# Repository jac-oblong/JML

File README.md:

# jml-16
16-bit computer built from scrap

## Design
The computer is designed in individual sections that come together to create the
whole system. This is useful as it makes changing a section easy.

## Parts
All parts have been scrapped from other computers/electronics. Using different
parts will likely produce a better computer.

### Changing parts
The high-level for this computer is designed in such a way that parts can easily
be swapped out for a different component with similar functionality. For 
example, the vga display driver can be swapped out for a different driver as
long as the inputs and outputs stay consistent.

Obviously, the hardware within specific modules cannot be swapped out as easily
without fully ensuring similar functionality.

## Folder Organization
Datasheets for parts, in addition to general documentation about the entire
project can be found in the [docs](/docs/) directory.

The assembler used to convert assembly to machine code can be found in the
[assembler](/assembler/) directory.

<!--
The compiler used to compile C code can be found in the [compiler](/compiler/)
directory.
-->

Information about the keyboard interface can be found in [keyboard](/keyboard/).

Information about the monitor interface can be found in [monitor](/monitor/).

Information about the different central computers can be found in any dirctory 
titled **jml-XX**.

Links to programs designed to be run on the **jml** family of computers can be 
found in [programs](/programs/)

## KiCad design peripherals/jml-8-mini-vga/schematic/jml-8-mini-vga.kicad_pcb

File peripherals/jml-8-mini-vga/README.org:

* JML-8-Mini VGA

#+ATTR_HTML: :width 600px
[[./schematic/jml-8-mini-vga.png]]

This provides a VGA interface to the JML-8-Mini via a Tang Nano 9k FPGA.
The daughterboard plugs into the the Z80 header pins on the JML-8-Mini.

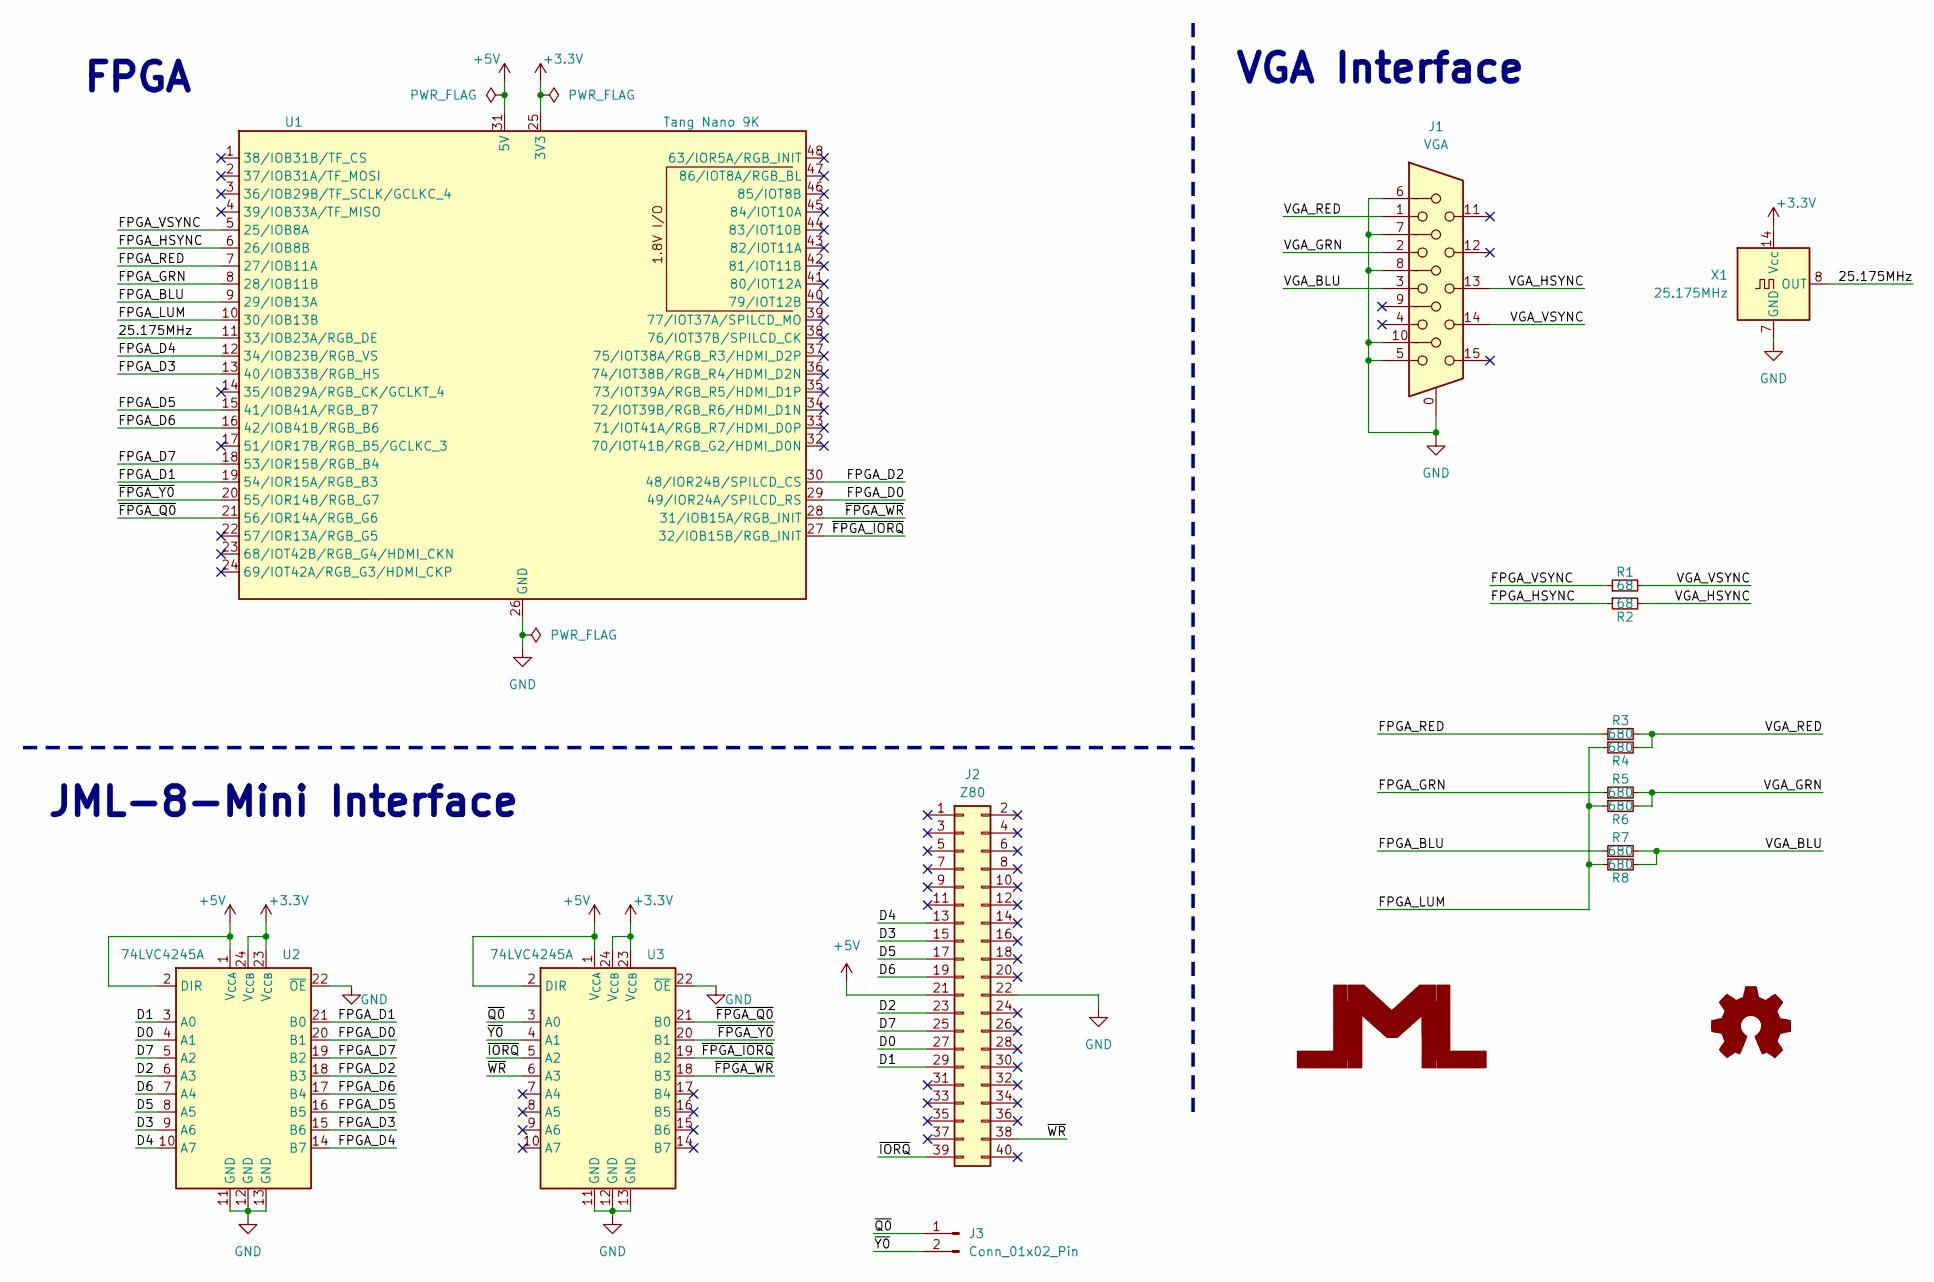
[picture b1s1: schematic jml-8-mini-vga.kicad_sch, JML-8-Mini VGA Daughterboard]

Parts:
J1: VGA; DSUB-15-HD_Female_Horizontal_P2.29x1.98mm_EdgePinOffset8.35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
J2: Z80; PinHeader_2x20_P2.54mm_Vertical
J3: Conn_01x02_Pin; PinHeader_1x02_P2.54mm_Vertical
R1, R2: 68; R_0805_2012Metric_Pad1.20x1.40mm_HandSolder
R3, R4, R5, R6, R7, R8: 680; R_0805_2012Metric_Pad1.20x1.40mm_HandSolder
U1: Tang Nano 9K; TangNano9k
U2, U3: 74LVC4245A; TSSOP-24_4.4x7.8mm_P0.65mm
X1: 25.175MHz; Oscillator_DIP-14

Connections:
+3.3V: U1.25 (3V3), U2.23 (V_{CCB}), U2.24 (V_{CCB}), U3.23 (V_{CCB}), U3.24 (V_{CCB}), X1.14 (Vcc)
+5V: J2.21, U1.31 (5V), U2.1 (V_{CCA}), U2.2 (DIR), U3.1 (V_{CCA}), U3.2 (DIR)
/25.175MHz: U1.11 (33/IOB23A/RGB_DE), X1.8 (OUT)
/D0: J2.27, U2.4 (A1)
/D1: J2.29, U2.3 (A0)
/D2: J2.23, U2.6 (A3)
/D3: J2.15, U2.9 (A6)
/D4: J2.13, U2.10 (A7)
/D5: J2.17, U2.8 (A5)
/D6: J2.19, U2.7 (A4)
/D7: J2.25, U2.5 (A2)
/FPGA_BLU: R7.1, U1.9 (29/IOB13A)
/FPGA_D0: U1.29 (49/IOR24A/SPILCD_RS), U2.20 (B1)
/FPGA_D1: U1.19 (54/IOR15A/RGB_B3), U2.21 (B0)
/FPGA_D2: U1.30 (48/IOR24B/SPILCD_CS), U2.18 (B3)
/FPGA_D3: U1.13 (40/IOB33B/RGB_HS), U2.15 (B6)
/FPGA_D4: U1.12 (34/IOB23B/RGB_VS), U2.14 (B7)
/FPGA_D5: U1.15 (41/IOB41A/RGB_B7), U2.16 (B5)
/FPGA_D6: U1.16 (42/IOB41B/RGB_B6), U2.17 (B4)
/FPGA_D7: U1.18 (53/IOR15B/RGB_B4), U2.19 (B2)
/FPGA_GRN: R5.1, U1.8 (28/IOB11B)
/FPGA_HSYNC: R2.1, U1.6 (26/IOB8B)
/FPGA_LUM: R4.1, R6.1, R8.1, U1.10 (30/IOB13B)
/FPGA_RED: R3.1, U1.7 (27/IOB11A)
/FPGA_VSYNC: R1.1, U1.5 (25/IOB8A)
/VGA_BLU: J1.3, R7.2, R8.2
/VGA_GRN: J1.2, R5.2, R6.2
/VGA_HSYNC: J1.13, R2.2
/VGA_RED: J1.1, R3.2, R4.2
/VGA_VSYNC: J1.14, R1.2
/~FPGA_IORQ: U1.27 (32/IOB15B/RGB_INIT), U3.19 (B2)
/~FPGA_Q0: U1.21 (56/IOR14A/RGB_G6), U3.21 (B0)
/~FPGA_WR: U1.28 (31/IOB15A/RGB_INIT), U3.18 (B3)
/~FPGA_Y0: U1.20 (55/IOR14B/RGB_G7), U3.20 (B1)
/~IORQ: J2.39, U3.5 (A2)
/~Q0: J3.1, U3.3 (A0)
/~WR: J2.38, U3.6 (A3)
/~Y0: J3.2, U3.4 (A1)
GND: J1.0, J1.5, J1.6, J1.7, J1.8, J1.10, J2.22, U1.26 (GND), U2.11 (GND), U2.12 (GND), U2.13 (GND), U2.22 (~OE), U3.11 (GND), U3.12 (GND), U3.13 (GND), U3.22 (~OE), X1.7 (GND)

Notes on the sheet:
VGA Interface
JML-8-Mini Interface
FPGA

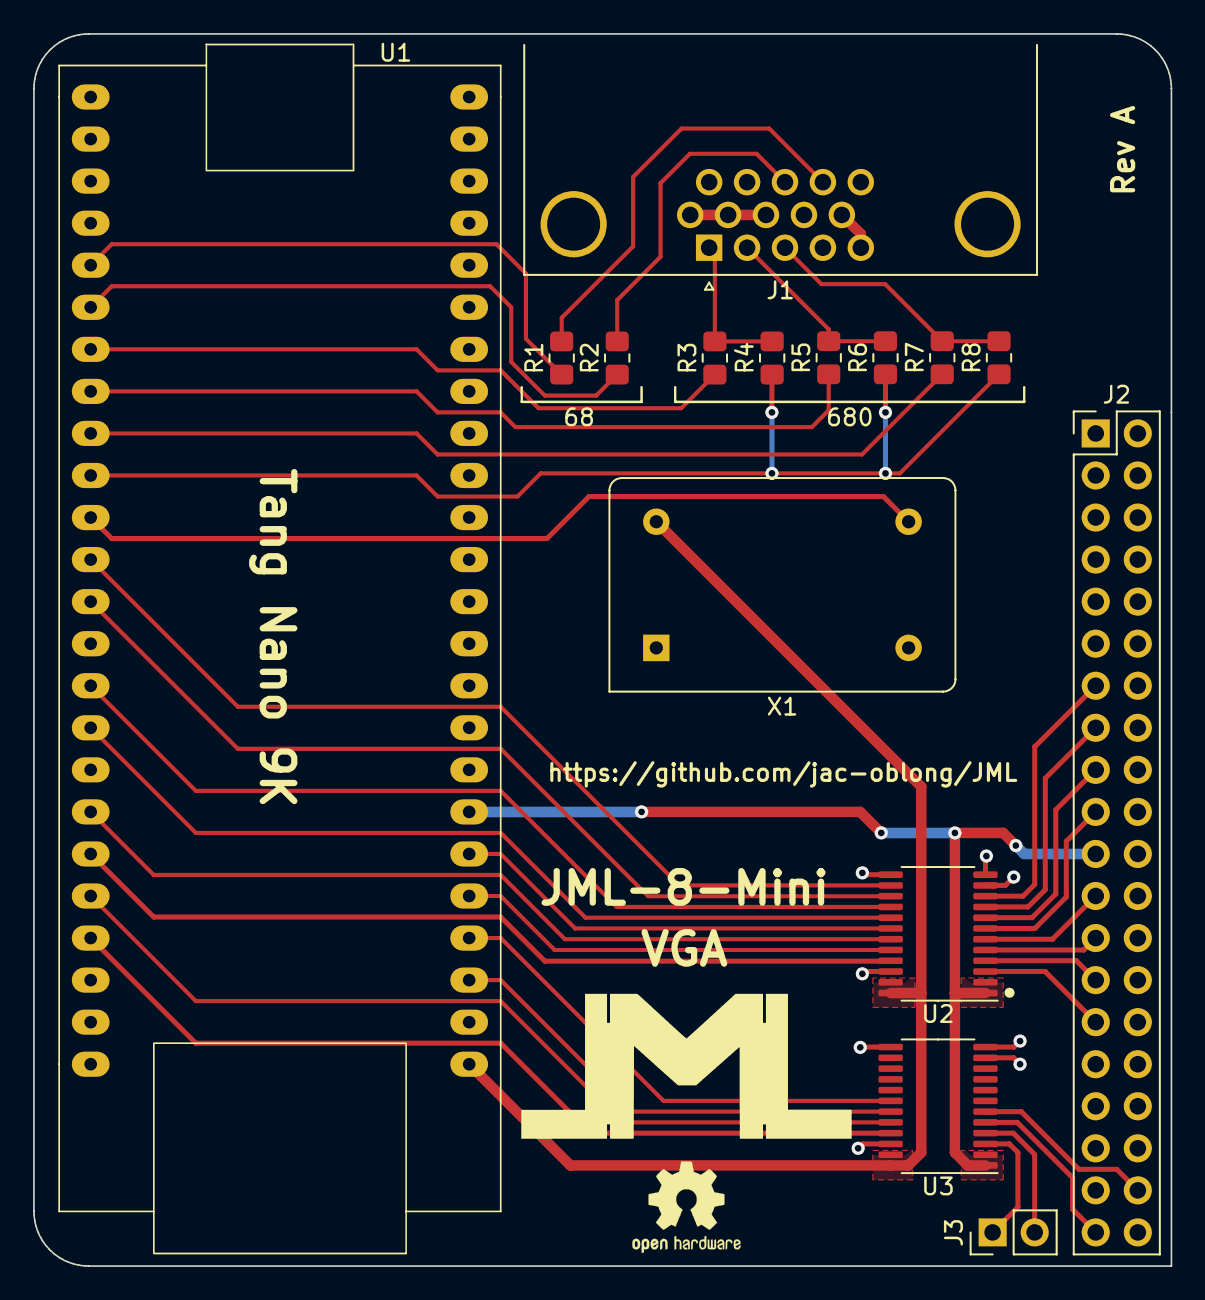
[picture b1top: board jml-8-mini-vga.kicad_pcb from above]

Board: 2 copper layers, 68.7 x 74.4 mm, 15 parts (0 on the bottom side), 39 nets.

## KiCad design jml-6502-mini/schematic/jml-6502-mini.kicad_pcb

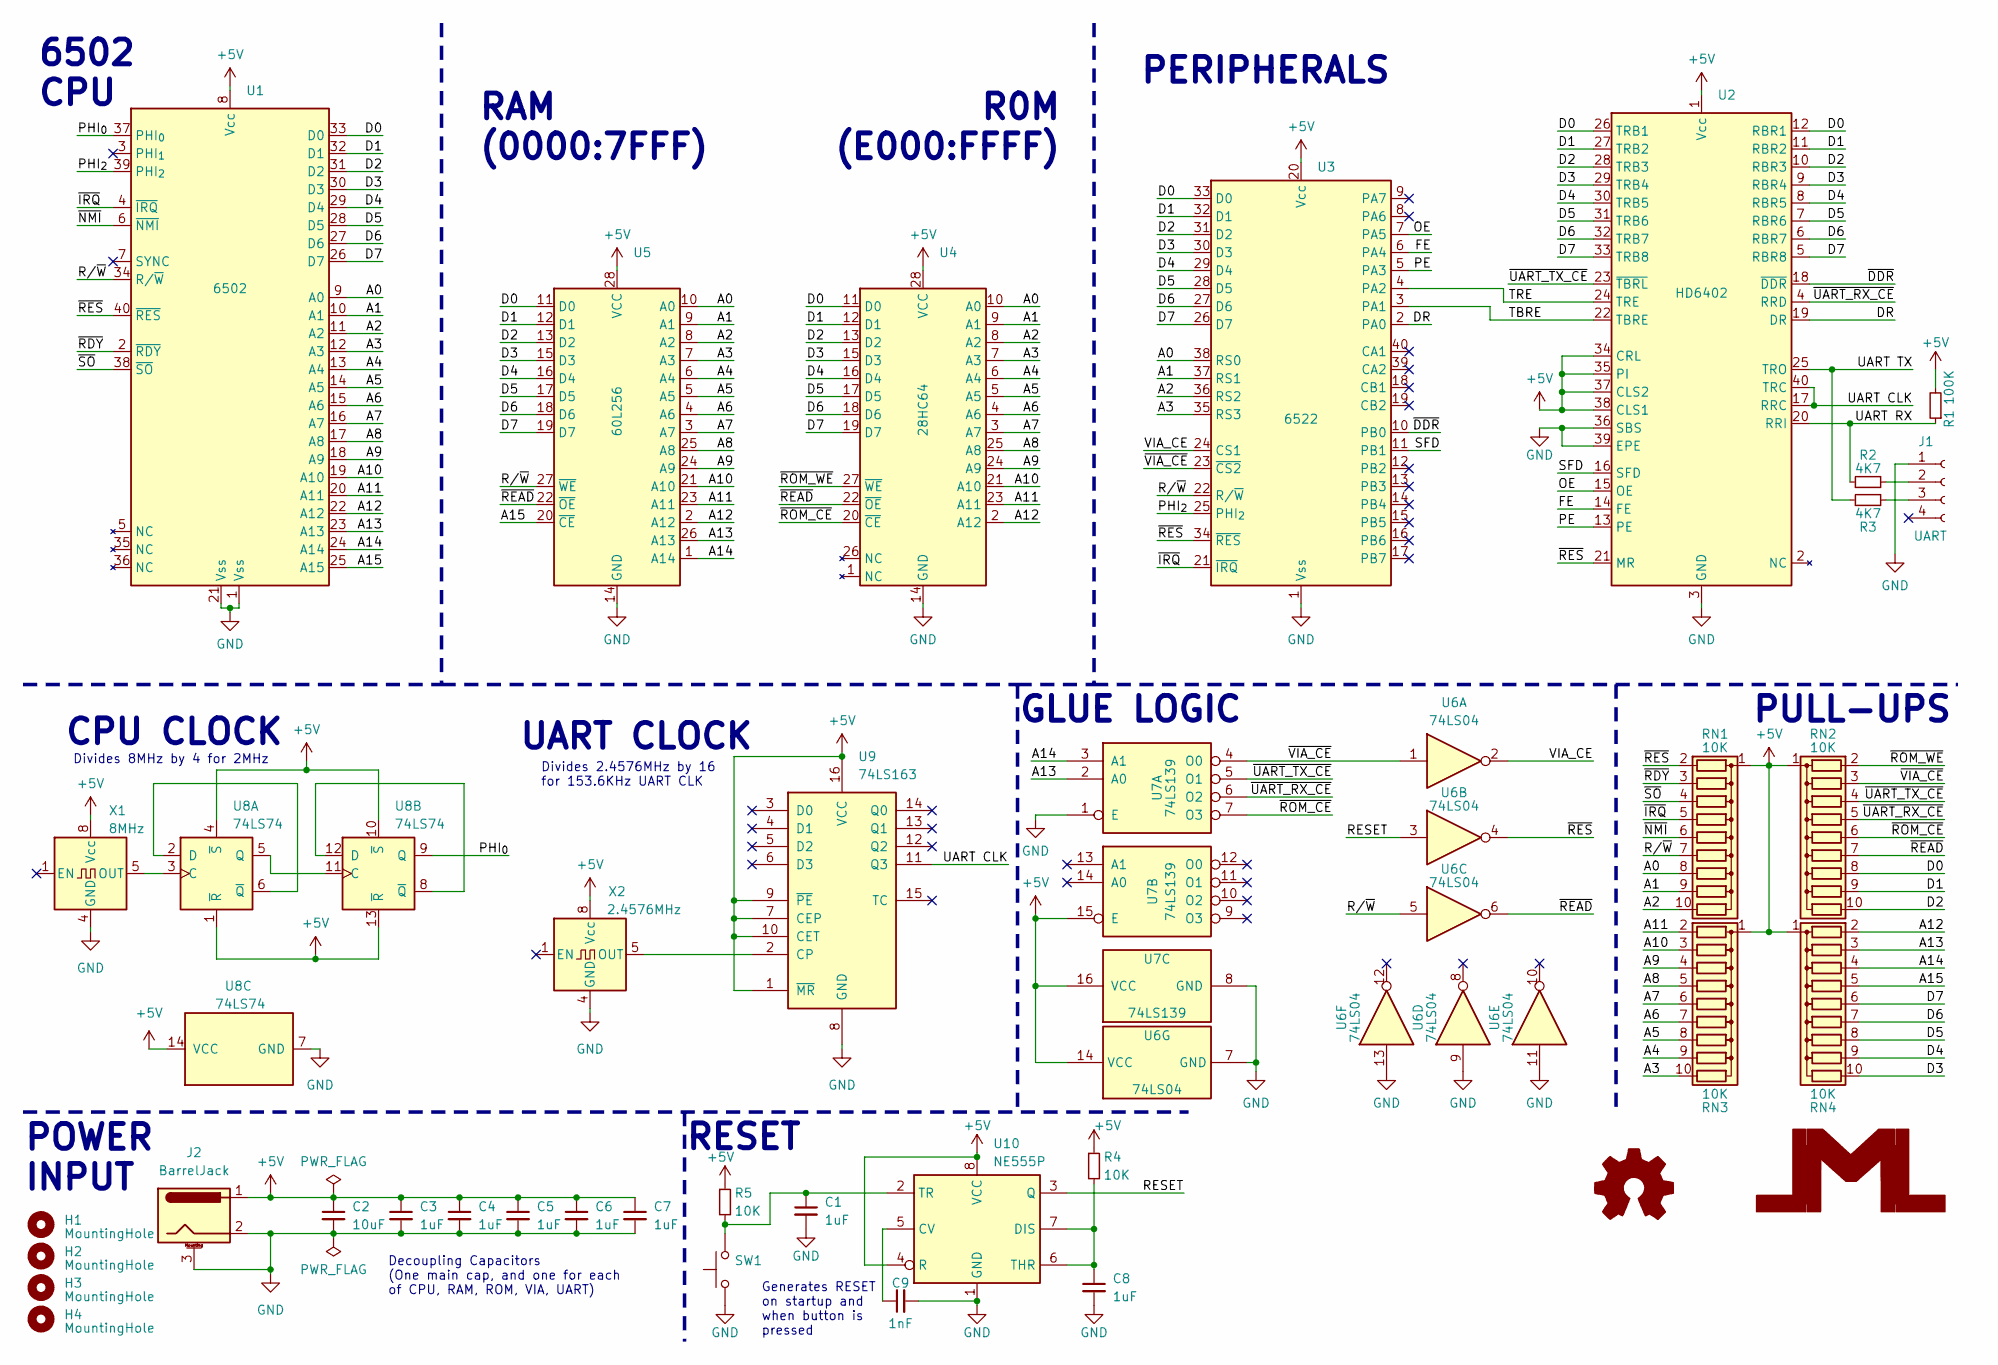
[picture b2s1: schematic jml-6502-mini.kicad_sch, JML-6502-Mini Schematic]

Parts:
C1, C3, C4, C5, C6, C7, C8: 1uF; C_Disc_D5.0mm_W2.5mm_P5.00mm
C2: 10uF; C_Radial_D5.0mm_H11.0mm_P2.00mm
C9: 1nF; C_Disc_D5.0mm_W2.5mm_P5.00mm
H1, H2, H3, H4: MountingHole; MountingHole_2.7mm_M2.5
J1: UART; PinHeader_1x04_P2.54mm_Horizontal
J2: BarrelJack; BarrelJack_Horizontal
R1: 100K; R_Axial_DIN0207_L6.3mm_D2.5mm_P7.62mm_Horizontal
R2, R3: 4K7; R_Axial_DIN0207_L6.3mm_D2.5mm_P7.62mm_Horizontal
R4, R5: 10K; R_Axial_DIN0207_L6.3mm_D2.5mm_P7.62mm_Horizontal
RN1, RN2, RN3, RN4: 10K; R_Array_SIP10
SW1: SW_Tactile_Straight_KSA0Axx1LFTR
U1: 6502; DIP-40_W15.24mm_Socket_LongPads
U2: HD6402; DIP-40_W15.24mm_Socket_LongPads
U3: 6522; DIP-40_W15.24mm_Socket_LongPads
U4: 28HC64; DIP-28_W15.24mm_Socket_LongPads
U5: 60L256; DIP-28_W15.24mm_Socket_LongPads
U6: 74LS04; DIP-14_W7.62mm_Socket_LongPads
U7: 74LS139; DIP-16_W7.62mm_Socket_LongPads
U8: 74LS74; DIP-14_W7.62mm_Socket_LongPads
U9: 74LS163; DIP-16_W7.62mm_Socket_LongPads
U10: NE555P; DIP-8_W7.62mm_Socket_LongPads
X1: 8MHz; Oscillator_DIP-8
X2: 2.4576MHz; Oscillator_DIP-8

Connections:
+5V: C2.1, C3.1, C4.1, C5.1, C6.1, C7.1, J2.1, R1.2, R4.1, R5.1, RN1.1 (common), RN2.1 (common), RN3.1 (common), RN4.1 (common), U1.8 (Vcc), U2.1 (Vcc), U2.34 (CRL), U2.35 (PI), U2.37 (CLS2), U2.38 (CLS1), U3.20 (Vcc), U4.28 (VCC), U5.28 (VCC), U6.14 (VCC), U7.15 (E), U7.16 (VCC), U8.1 (~R), U8.4 (~S), U8.10 (~S), U8.13 (~R), U8.14 (VCC), U9.1 (~MR), U9.7 (CEP), U9.9 (~PE), U9.10 (CET), U9.16 (VCC), U10.4 (R), U10.8 (VCC), X1.8 (Vcc), X2.8 (Vcc)
/A0: RN1.8 (R7), U1.9 (A0), U3.38 (RS0), U4.10 (A0), U5.10 (A0)
/A1: RN1.9 (R8), U1.10 (A1), U3.37 (RS1), U4.9 (A1), U5.9 (A1)
/A2: RN1.10 (R9), U1.11 (A2), U3.36 (RS2), U4.8 (A2), U5.8 (A2)
/A3: RN3.10 (R9), U1.12 (A3), U3.35 (RS3), U4.7 (A3), U5.7 (A3)
/A4: RN3.9 (R8), U1.13 (A4), U4.6 (A4), U5.6 (A4)
/A5: RN3.8 (R7), U1.14 (A5), U4.5 (A5), U5.5 (A5)
/A6: RN3.7 (R6), U1.15 (A6), U4.4 (A6), U5.4 (A6)
/A7: RN3.6 (R5), U1.16 (A7), U4.3 (A7), U5.3 (A7)
/A8: RN3.5 (R4), U1.17 (A8), U4.25 (A8), U5.25 (A8)
/A9: RN3.4 (R3), U1.18 (A9), U4.24 (A9), U5.24 (A9)
/A10: RN3.3 (R2), U1.19 (A10), U4.21 (A10), U5.21 (A10)
/A11: RN3.2 (R1), U1.20 (A11), U4.23 (A11), U5.23 (A11)
/A12: RN4.2 (R1), U1.22 (A12), U4.2 (A12), U5.2 (A12)
/A13: RN4.3 (R2), U1.23 (A13), U5.26 (A13), U7.2 (A0)
/A14: RN4.4 (R3), U1.24 (A14), U5.1 (A14), U7.3 (A1)
/A15: RN4.5 (R4), U1.25 (A15), U5.20 (~CE)
/D0: RN2.8 (R7), U1.33 (D0), U2.12 (RBR1), U2.26 (TRB1), U3.33 (D0), U4.11 (D0), U5.11 (D0)
/D1: RN2.9 (R8), U1.32 (D1), U2.11 (RBR2), U2.27 (TRB2), U3.32 (D1), U4.12 (D1), U5.12 (D1)
/D2: RN2.10 (R9), U1.31 (D2), U2.10 (RBR3), U2.28 (TRB3), U3.31 (D2), U4.13 (D2), U5.13 (D2)
/D3: RN4.10 (R9), U1.30 (D3), U2.9 (RBR4), U2.29 (TRB4), U3.30 (D3), U4.15 (D3), U5.15 (D3)
/D4: RN4.9 (R8), U1.29 (D4), U2.8 (RBR5), U2.30 (TRB5), U3.29 (D4), U4.16 (D4), U5.16 (D4)
/D5: RN4.8 (R7), U1.28 (D5), U2.7 (RBR6), U2.31 (TRB6), U3.28 (D5), U4.17 (D5), U5.17 (D5)
/D6: RN4.7 (R6), U1.27 (D6), U2.6 (RBR7), U2.32 (TRB7), U3.27 (D6), U4.18 (D6), U5.18 (D6)
/D7: RN4.6 (R5), U1.26 (D7), U2.5 (RBR8), U2.33 (TRB8), U3.26 (D7), U4.19 (D7), U5.19 (D7)
/DR: U2.19 (DR), U3.2 (PA0)
/FE: U2.14 (FE), U3.6 (PA4)
/OE: U2.15 (OE), U3.7 (PA5)
/PE: U2.13 (PE), U3.5 (PA3)
/PHI_{0}: U1.37 (PHI_{0}), U8.9 (Q)
/PHI_{2}: U1.39 (PHI_{2}), U3.25 (PHI_{2})
/RESET: U6.3, U10.3 (Q)
/R/~W: RN1.7 (R6), U1.34 (R/~W), U3.22 (R/~W), U5.27 (~WE), U6.5
/SFD: U2.16 (SFD), U3.11 (PB1)
/TBRE: U2.22 (TBRE), U3.3 (PA1)
/TRE: U2.24 (TRE), U3.4 (PA2)
/UART CLK: U2.17 (RRC), U2.40 (TRC), U9.11 (Q3)
/UART RX: R1.1, R2.1, U2.20 (RRI)
/UART TX: R3.1, U2.25 (TRO)
/VIA_CE: U3.24 (CS1), U6.2
/~DDR: U2.18 (~DDR), U3.10 (PB0)
/~IRQ: RN1.5 (R4), U1.4 (~IRQ), U3.21 (~IRQ)
/~NMI: RN1.6 (R5), U1.6 (~NMI)
/~RDY: RN1.3 (R2), U1.2 (~RDY)
/~READ: RN2.7 (R6), U4.22 (~OE), U5.22 (~OE), U6.6
/~RES: RN1.2 (R1), U1.40 (~RES), U2.21 (MR), U3.34 (~RES), U6.4
/~ROM_CE: RN2.6 (R5), U4.20 (~CE), U7.7 (O3)
/~ROM_WE: RN2.2 (R1), U4.27 (~WE)
/~SO: RN1.4 (R3), U1.38 (~SO)
/~UART_RX_CE: RN2.5 (R4), U2.4 (RRD), U7.6 (O2)
/~UART_TX_CE: RN2.4 (R3), U2.23 (~TBRL), U7.5 (O1)
/~VIA_CE: RN2.3 (R2), U3.23 (~CS2), U6.1, U7.4 (O0)
GND: C1.2, C2.2, C3.2, C4.2, C5.2, C6.2, C7.2, C8.2, C9.2, J1.1, J2.2, J2.3 (MountPin), SW1.1, U1.1 (Vss), U1.21 (Vss), U2.3 (GND), U2.36 (SBS), U2.39 (EPE), U3.1 (Vss), U4.14 (GND), U5.14 (GND), U6.7 (GND), U6.9, U6.11, U6.13, U7.1 (E), U7.8 (GND), U8.7 (GND), U9.8 (GND), U10.1 (GND), X1.4 (GND), X2.4 (GND)
unnamed: J1.2, R2.2
unnamed: J1.3, R3.2
unnamed: U8.3 (C), X1.5 (OUT)
unnamed: U8.2 (D), U8.6 (~Q)
unnamed: U8.5 (Q), U8.11 (C)
unnamed: U8.8 (~Q), U8.12 (D)
unnamed: U9.2 (CP), X2.5 (OUT)
unnamed: C9.1, U10.5 (CV)
unnamed: C8.1, R4.2, U10.6 (THR), U10.7 (DIS)
unnamed: C1.1, R5.2, SW1.2, U10.2 (TR)

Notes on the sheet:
GLUE LOGIC
RAM (0000:7FFF)
R0M (E000:FFFF)
RESET
Generates RESET on startup and when button is pressed
Divides 8MHz by 4 for 2MHz
CPU CLOCK
POWER INPUT
UART CLOCK
Decoupling Capacitors (One main cap, and one for each of CPU, RAM, ROM, VIA, UART)
Divides 2.4576MHz by 16 for 153.6KHz UART CLK
6502 CPU
PULL-UPS
PERIPHERALS

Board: 4 copper layers, 37 parts (0 on the bottom side), 63 nets, no tracks yet.

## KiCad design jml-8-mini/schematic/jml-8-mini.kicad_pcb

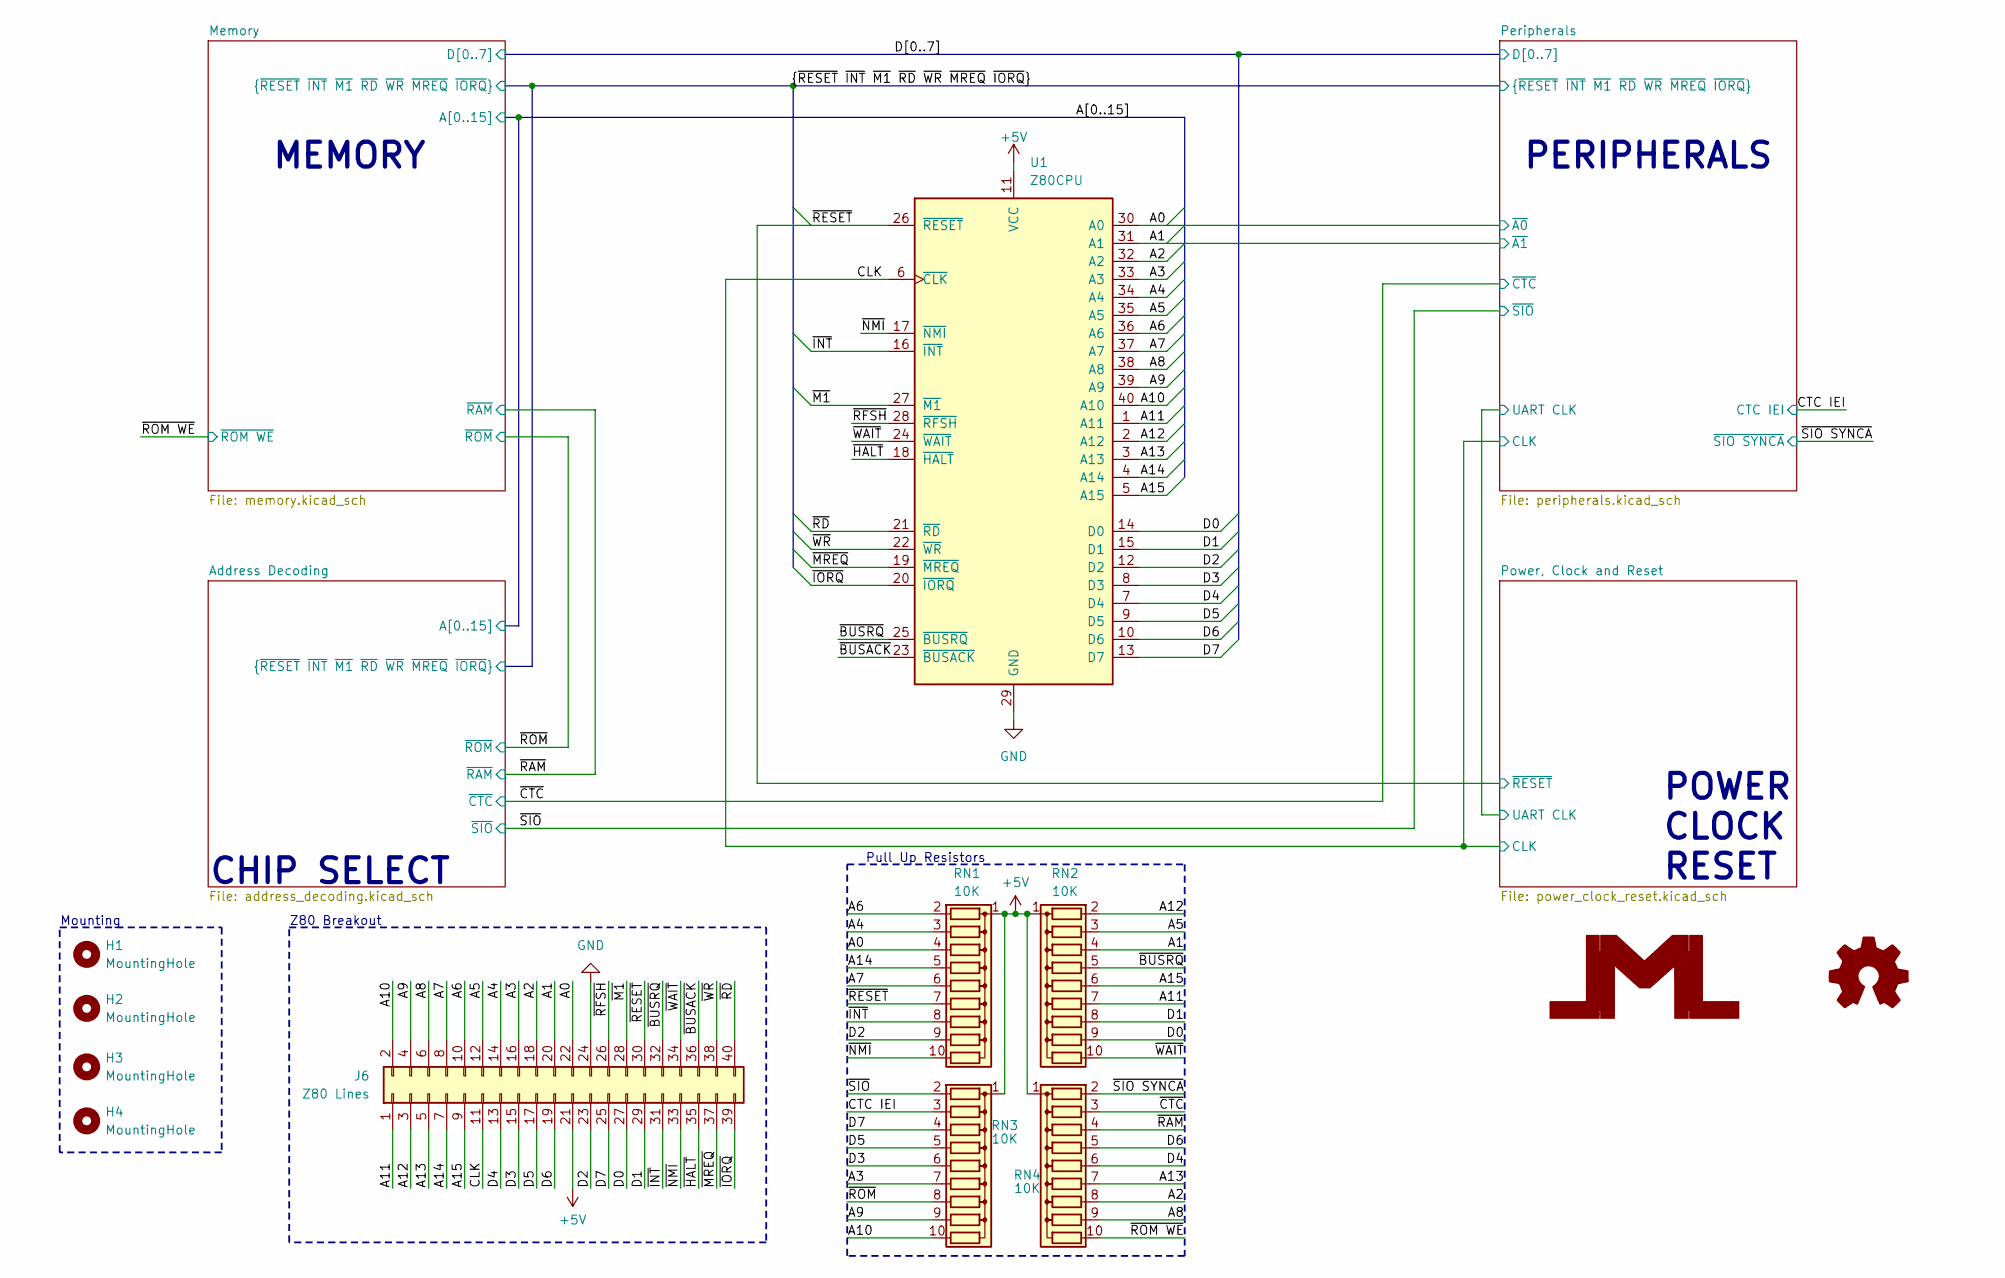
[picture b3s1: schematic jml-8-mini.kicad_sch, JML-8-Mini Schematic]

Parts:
H1, H2, H3, H4: MountingHole; MountingHole_2.7mm_M2.5
J6: Z80 Lines; PinHeader_2x20_P2.54mm_Vertical
RN1, RN2, RN3, RN4: 10K; R_Array_SIP10
U1: Z80CPU; DIP-40_W15.24mm_Socket_LongPads

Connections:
/A0: J6.22, RN1.4 (R3), U1.30 (A0); also elsewhere on the board
/A1: J6.20, RN2.4 (R3), U1.31 (A1); also elsewhere on the board
/A2: J6.18, RN4.8 (R7), U1.32 (A2); also elsewhere on the board
/A3: J6.16, RN3.7 (R6), U1.33 (A3); also elsewhere on the board
/A4: J6.14, RN1.3 (R2), U1.34 (A4); also elsewhere on the board
/A5: J6.12, RN2.3 (R2), U1.35 (A5); also elsewhere on the board
/A6: J6.10, RN1.2 (R1), U1.36 (A6); also elsewhere on the board
/A7: J6.8, RN1.6 (R5), U1.37 (A7); also elsewhere on the board
/A8: J6.6, RN4.9 (R8), U1.38 (A8); also elsewhere on the board
/A9: J6.4, RN3.9 (R8), U1.39 (A9); also elsewhere on the board
/A10: J6.2, RN3.10 (R9), U1.40 (A10); also elsewhere on the board
/A11: J6.1, RN2.7 (R6), U1.1 (A11); also elsewhere on the board
/A12: J6.3, RN2.2 (R1), U1.2 (A12); also elsewhere on the board
/A13: J6.5, RN4.7 (R6), U1.3 (A13); also elsewhere on the board
/A14: J6.7, RN1.5 (R4), U1.4 (A14); also elsewhere on the board
/CLK: J6.11, U1.6 (~CLK); also elsewhere on the board
/CTC IEI: RN3.3 (R2); also elsewhere on the board
/D0: J6.27, RN2.9 (R8), U1.14 (D0); also elsewhere on the board
/D1: J6.29, RN2.8 (R7), U1.15 (D1); also elsewhere on the board
/D2: J6.23, RN1.9 (R8), U1.12 (D2); also elsewhere on the board
/D3: J6.15, RN3.6 (R5), U1.8 (D3); also elsewhere on the board
/D4: J6.13, RN4.6 (R5), U1.7 (D4); also elsewhere on the board
/D5: J6.17, RN3.5 (R4), U1.9 (D5); also elsewhere on the board
/D6: J6.19, RN4.5 (R4), U1.10 (D6); also elsewhere on the board
/D7: J6.25, RN3.4 (R3), U1.13 (D7); also elsewhere on the board
/~BUSACK: J6.36, U1.23 (~BUSACK)
/~BUSRQ: J6.32, RN2.5 (R4), U1.25 (~BUSRQ)
/~CTC: RN4.3 (R2); also elsewhere on the board
/~HALT: J6.35, U1.18 (~HALT)
/~INT: J6.31, RN1.8 (R7), U1.16 (~INT); also elsewhere on the board
/~IORQ: J6.39, U1.20 (~IORQ); also elsewhere on the board
/~M1: J6.28, U1.27 (~M1); also elsewhere on the board
/~MREQ: J6.37, U1.19 (~MREQ); also elsewhere on the board
/~NMI: J6.33, RN1.10 (R9), U1.17 (~NMI)
/~RAM: RN4.4 (R3); also elsewhere on the board
/~RD: J6.40, U1.21 (~RD); also elsewhere on the board
/~RFSH: J6.26, U1.28 (~RFSH)
/~ROM WE: RN4.10 (R9); also elsewhere on the board
/~ROM: RN3.8 (R7); also elsewhere on the board
/~SIO SYNCA: RN4.2 (R1); also elsewhere on the board
/~SIO: RN3.2 (R1); also elsewhere on the board
/~WAIT: J6.34, RN2.10 (R9), U1.24 (~WAIT)
/~WR: J6.38, U1.22 (~WR); also elsewhere on the board

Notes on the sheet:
MEMORY
PERIPHERALS
CHIP SELECT
POWER CLOCK RESET
Z80 Breakout
Mounting
Pull Up Resistors

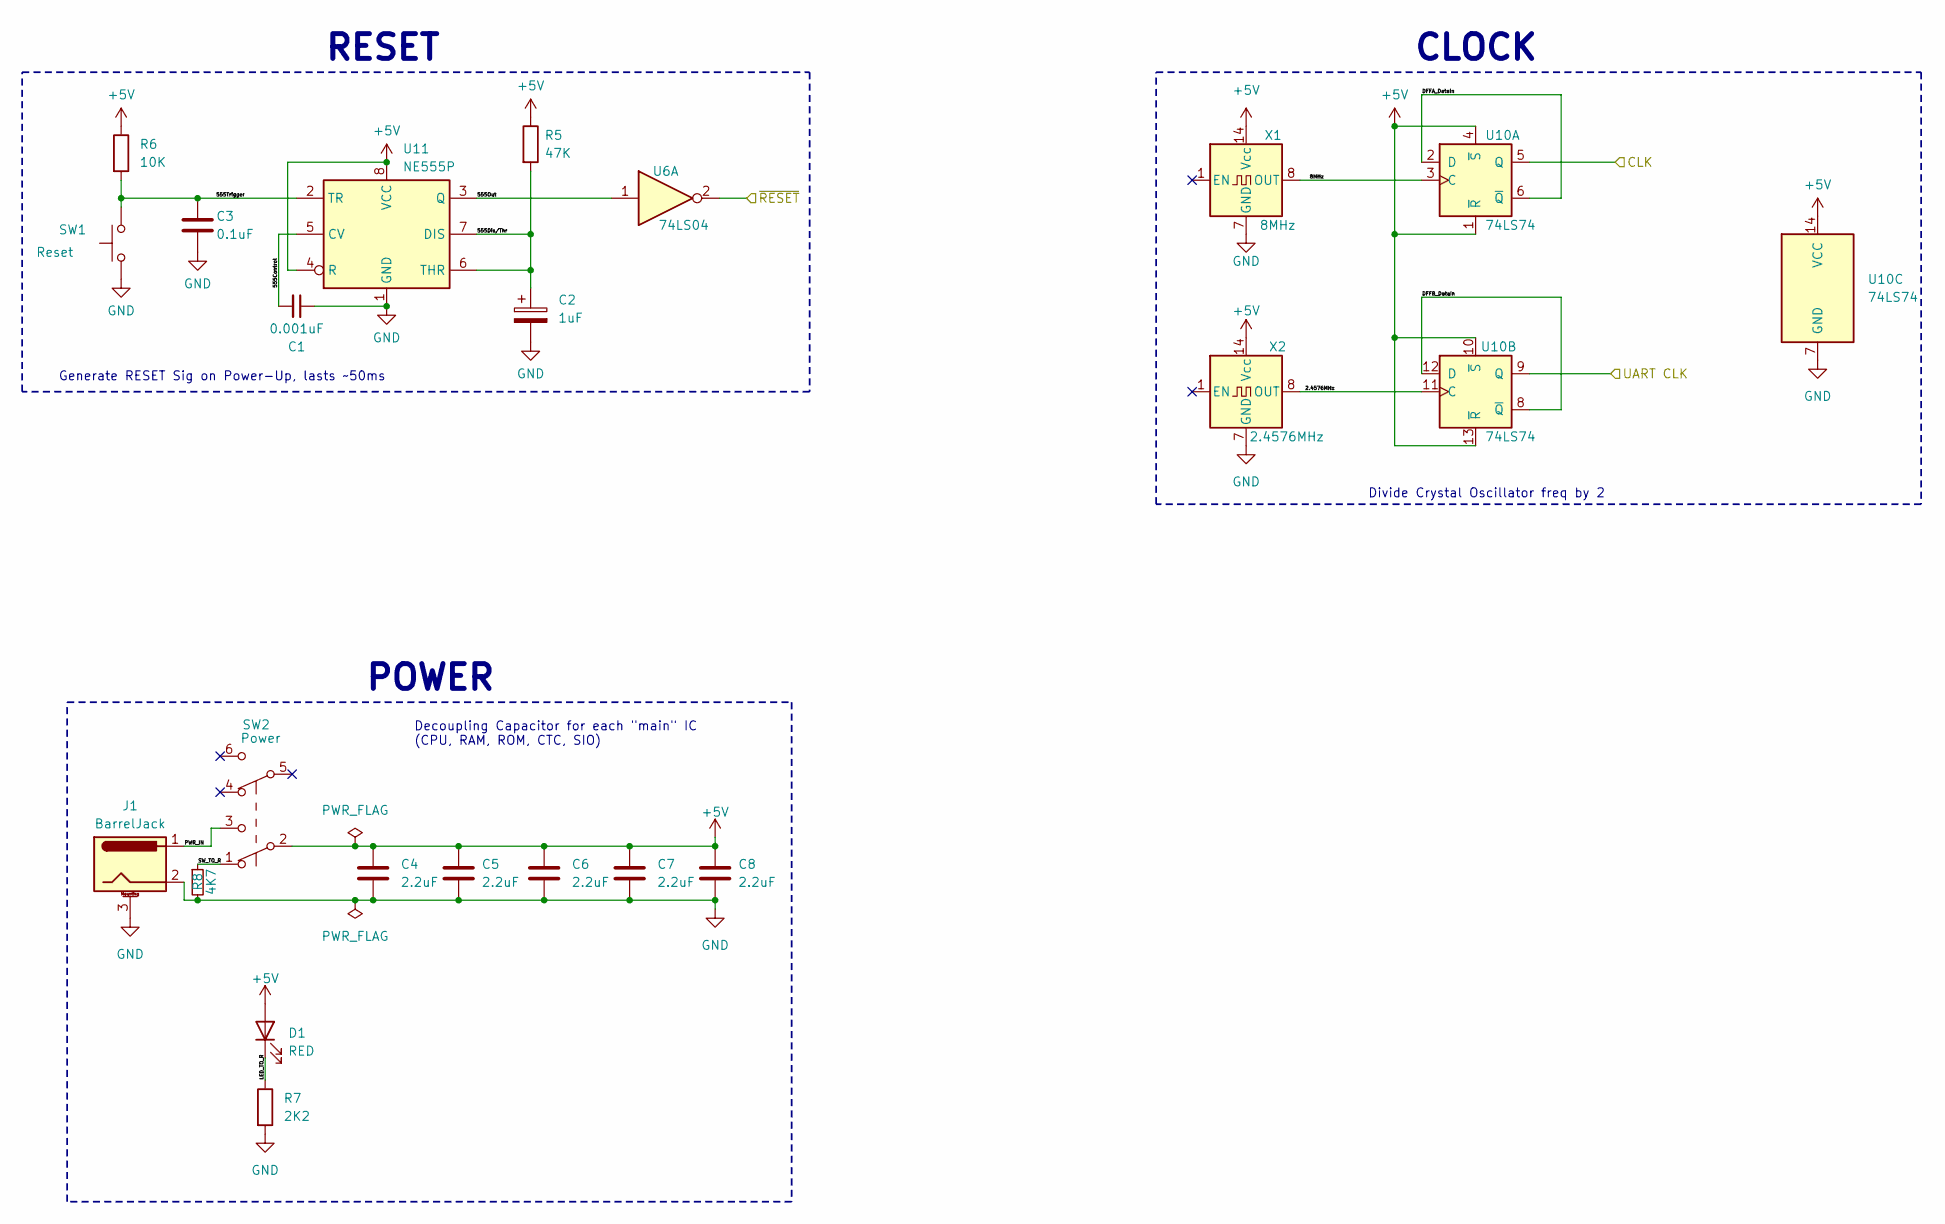
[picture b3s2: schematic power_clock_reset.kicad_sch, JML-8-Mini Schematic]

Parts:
C1: 0.001uF; C_Disc_D5.0mm_W2.5mm_P5.00mm
C2: 1uF; CP_Radial_D5.0mm_P2.50mm
C3: 0.1uF; C_Disc_D5.0mm_W2.5mm_P5.00mm
C4, C5, C6, C7, C8: 2.2uF; C_Disc_D5.0mm_W2.5mm_P5.00mm
D1: RED; LED_D5.0mm
J1: BarrelJack; BarrelJack_Horizontal
R5: 47K; R_Axial_DIN0207_L6.3mm_D2.5mm_P7.62mm_Horizontal
R6: 10K; R_Axial_DIN0207_L6.3mm_D2.5mm_P7.62mm_Horizontal
R7: 2K2; R_Axial_DIN0207_L6.3mm_D2.5mm_P7.62mm_Horizontal
R8: 4K7; R_Axial_DIN0207_L6.3mm_D2.5mm_P7.62mm_Horizontal
SW1: Reset; SW_Tactile_Straight_KSA0Axx1LFTR
SW2: Power; SW_Push_2P2T_Toggle_CK_PVA2xxH1xxxxxxV2
U6: 74LS04; DIP-14_W7.62mm_Socket_LongPads
U10: 74LS74; DIP-14_W7.62mm_Socket_LongPads
U11: NE555P; DIP-8_W7.62mm_Socket_LongPads
X1: 8MHz; Oscillator_DIP-14
X2: 2.4576MHz; Oscillator_DIP-14

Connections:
/CLK: U10.5 (Q); also elsewhere on the board
/Peripherals/UART CLK: U10.9 (Q); also elsewhere on the board
/Power, Clock and Reset/2.4576MHz: U10.11 (C), X2.8 (OUT)
/Power, Clock and Reset/8MHz: U10.3 (C), X1.8 (OUT)
/Power, Clock and Reset/555Control: C1.2, U11.5 (CV)
/Power, Clock and Reset/555Dis/Thr: C2.1, R5.2, U11.6 (THR), U11.7 (DIS)
/Power, Clock and Reset/555Trigger: C3.1, R6.2, SW1.2, U11.2 (TR)
/Power, Clock and Reset/DFFA_DataIn: U10.2 (D), U10.6 (~Q)
/Power, Clock and Reset/DFFB_DataIn: U10.8 (~Q), U10.12 (D)
/Power, Clock and Reset/LED_TO_R: D1.1 (K), R7.1
/Power, Clock and Reset/PWR_IN: J1.1, SW2.3 (C)
/Power, Clock and Reset/SW_TO_R: R8.1, SW2.1 (A)

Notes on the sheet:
Generate RESET Sig on Power-Up, lasts ~50ms
RESET
CLOCK
POWER
Divide Crystal Oscillator freq by 2
Decoupling Capacitor for each "main" IC (CPU, RAM, ROM, CTC, SIO)

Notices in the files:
jml-6502-mini/schematic/jml-6502-mini.kicad_sch:
Released under MIT License
